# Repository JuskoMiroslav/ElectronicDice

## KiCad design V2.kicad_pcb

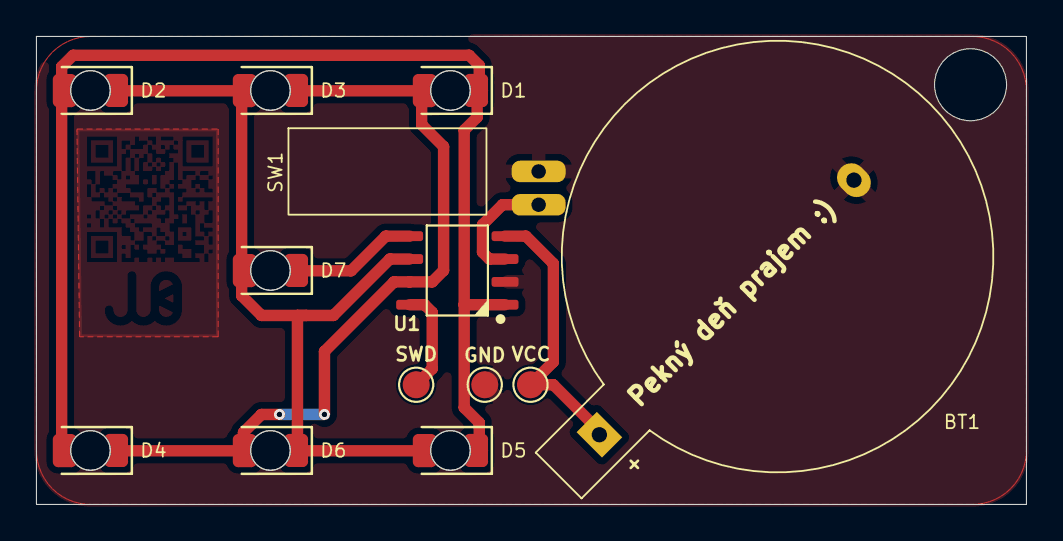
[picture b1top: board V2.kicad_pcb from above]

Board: 2 copper layers, 55.0 x 26.0 mm, 13 parts (0 on the bottom side), 8 nets.

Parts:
BT1: Battery_Cell; ds1092-05b6p
D1, D2, D3, D4, D5, D6, D7: LED
GND: TestPoint; TestPoint_Pad_D1.5mm
SW1: SW_SPST; SW-18020
SWD: TestPoint; TestPoint_Pad_D1.5mm
U1: CH32V003JxMx; JEITA_SOIC-8_3.9x4.9mm_P1.27mm
VCC: TestPoint; TestPoint_Pad_D1.5mm

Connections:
+BATT: BT1.1 (+), U1.4 (VDD), VCC.1 (1_1)
/PA1: D1.1 (K), D2.2 (A), D4.2 (A), D5.1 (K), U1.1 (PD6/PA1)
/PA2: SW1.2 (B), U1.3 (PA2)
/PC1: D7.1 (K), U1.5 (PC1)
/PC2: D2.1 (K), D3.2 (A), D5.2 (A), D6.1 (K), D7.2 (A), U1.6 (PC2)
/PC4: D1.2 (A), D3.1 (K), D4.1 (K), D6.2 (A), U1.7 (PC4)
/PD1: SWD.1 (1_1), U1.8 (PD1/PD4/PD5)
GND: BT1.2 (-), GND.1 (1_1), SW1.1 (A), U1.2 (VSS)

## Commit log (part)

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2026-05-27 final?
2026-05-28 final v2
